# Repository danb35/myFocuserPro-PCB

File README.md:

# myFocuserPro-PCB
 KiCad schematic and board for myFocuserPro2: https://sourceforge.net/projects/arduinofocuscontrollerpro/

# Introduction
myFocuserPro is a DIY, Arduino-based focuser designed for use with telescopes.  The design, source code, schematics, PCB files (Gerbers), and extensive documentation are available at the link above.  So what am I doing in this repo?

Unfortunately, the Gerbers there have a few issues, most notably that the footprint for the reverse-polarity protection diode (D1 on the schematic) just doesn't fit the specified diode.  The specified "fix" for the problem is to file down the leads of the diode until they fit through the holes.  And while this should be a trivial thing to fix, editable source files for the schematic and board haven't been released.

To address this, I re-drew the schematic and PCB layout in KiCad 6.0.  [KiCad](https://www.kicad.org/) is free, open source electronics design software, so you can download it to edit these files as desired.

# Design changes
This schematic is identical to the M-MT-F-BT DRV8825-HW203 variation at SourceForge, as that's the recommended version for new builds.  I intend (and hope) that the schematic will be easier to read and follow, but there should not be any changes in the components or how they're connected.  I don't intend to do this for any other variations of the schematic.  Most of the reference designators (i.e., R3, C2, etc.) are identical, but KiCad has changed some of the semiconductors.  But I've made a few changes to the board layout.

First, of course, there's the change that drove the whole redesign--the footprint for D1 now actually fits the specified diode.  I've also replaced most of the places where pin headers had been used for off-board connections (e.g., for the stepper, the pushbuttons, the display, etc.) and replaced them with JST-XH connectors.  These provide some friction to prevent connections from coming loose inadvertently, and also polarize the connections (so, e.g., you can't plug in a LED backward).  The only exception to this is J3, the programming "switch."  I intend that this will be a jumper, not an externally accessible switch.

While the board size is similar to the original, it is not identical, and it will not fit in the 3D-printed case design that's posted on SourceForge.  As time permits, I'll try to prepare a case design that will work with this.

# Board Images
Here are images of the front and back of the board:

And here are 3D renders of (mostly) populated boards:

# Ordering
I don't sell these boards; you can have them made by any PCB fab you choose.  To do so, simply download Gerber/myFocuserPro.zip from this repo, upload it to your fab of choice, and have at it.  If you don't have a fab of choice, consider the two linked below, in which I have no financial interest (i.e., I'm not an affiliate, partner, or anything else; I don't make anything from your purchase of these boards--I'm just a customer of both services).

## OSHPark
OSHPark are an American company known for high-quality boards.  They'll produce three copies of your design for $5 per square inch, in purple, with gold plating.  This cost is often higher than the Chinese fabs, but they don't charge shipping, and you don't have to wait for shipping for China.  This board costs about $27 shipped for three copies as of this writing.  You can order boards using this link:
https://oshpark.com/profiles/danb35

## JLCPCB
[JLCPCB](https://jlcpcb.com/) are a Chinese PCB fab that I've been pretty happy with.  Their prices are low (starting at $2/5 boards), they produce the boards quickly, and they ship quickly via DHL.  The biggest drawback is the cost of shipping--at this writing, five boards will cost you $2, but the shipping is another $20 or more.

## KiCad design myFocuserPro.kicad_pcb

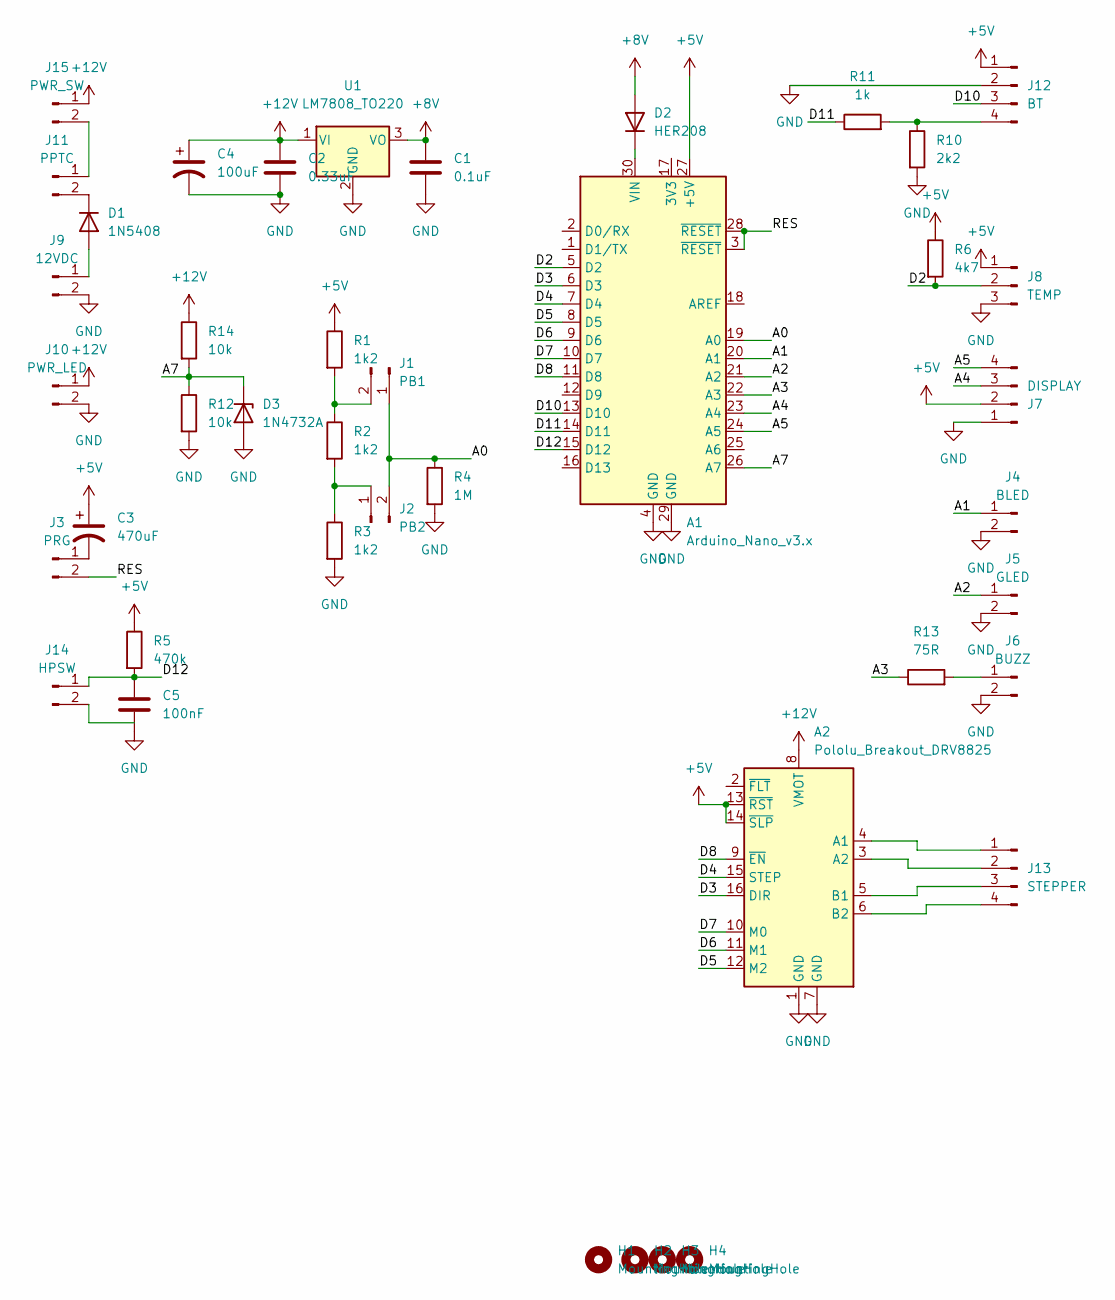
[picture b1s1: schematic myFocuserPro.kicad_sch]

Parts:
A1: Arduino_Nano_v3.x; Arduino_Nano
A2: Pololu_Breakout_DRV8825; Pololu_Breakout-16_15.2x20.3mm
C1: 0.1uF; C_Disc_D6.0mm_W2.5mm_P5.00mm
C2: 0.33uF; C_Disc_D6.0mm_W2.5mm_P5.00mm
C3: 470uF; CP_Radial_D8.0mm_P3.50mm
C4: 100uF; CP_Radial_D8.0mm_P3.50mm
C5: 100nF; C_Disc_D6.0mm_W2.5mm_P5.00mm
D1: 1N5408; D_DO-201AD_P15.24mm_Horizontal
D2: HER208; D_DO-15_P12.70mm_Horizontal
D3: 1N4732A; D_DO-15_P12.70mm_Horizontal
H1, H2, H3, H4: MountingHole; MountingHole_3.2mm_M3
J1: PB1; JST_XH_B2B-XH-AM_1x02_P2.50mm_Vertical
J2: PB2; JST_XH_B2B-XH-AM_1x02_P2.50mm_Vertical
J3: PRG; PinHeader_1x02_P2.54mm_Vertical
J4: BLED; JST_XH_B2B-XH-AM_1x02_P2.50mm_Vertical
J5: GLED; JST_XH_B2B-XH-AM_1x02_P2.50mm_Vertical
J6: BUZZ; JST_XH_B2B-XH-AM_1x02_P2.50mm_Vertical
J7: DISPLAY; JST_XH_B4B-XH-AM_1x04_P2.50mm_Vertical
J8: TEMP; JST_XH_B3B-XH-AM_1x03_P2.50mm_Vertical
J9: 12VDC; JST_XH_B2B-XH-AM_1x02_P2.50mm_Vertical
J10: PWR_LED; JST_XH_B2B-XH-AM_1x02_P2.50mm_Vertical
J11: PPTC; JST_XH_B2B-XH-AM_1x02_P2.50mm_Vertical
J12: BT; JST_XH_B4B-XH-AM_1x04_P2.50mm_Vertical
J13: STEPPER; JST_XH_B4B-XH-AM_1x04_P2.50mm_Vertical
J14: HPSW; JST_XH_B2B-XH-AM_1x02_P2.50mm_Vertical
J15: PWR_SW; JST_XH_B2B-XH-AM_1x02_P2.50mm_Vertical
R1, R2, R3: 1k2; R_Axial_DIN0309_L9.0mm_D3.2mm_P2.54mm_Vertical
R4: 1M; R_Axial_DIN0309_L9.0mm_D3.2mm_P12.70mm_Horizontal
R5: 470k; R_Axial_DIN0309_L9.0mm_D3.2mm_P2.54mm_Vertical
R6: 4k7; R_Axial_DIN0309_L9.0mm_D3.2mm_P12.70mm_Horizontal
R10: 2k2; R_Axial_DIN0309_L9.0mm_D3.2mm_P2.54mm_Vertical
R11: 1k; R_Axial_DIN0309_L9.0mm_D3.2mm_P2.54mm_Vertical
R12, R14: 10k; R_Axial_DIN0309_L9.0mm_D3.2mm_P12.70mm_Horizontal
R13: 75R; R_Axial_DIN0309_L9.0mm_D3.2mm_P12.70mm_Horizontal
U1: LM7808_TO220; TO-220-3_Vertical

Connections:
+5V: A1.27 (+5V), A2.13 (~RST), A2.14 (~SLP), C3.1, J7.2, J8.1, J12.1, R1.1, R5.1, R6.1
+8V: C1.1, D2.2 (A), U1.3 (VO)
+12V: A2.8 (VMOT), C2.1, C4.1, J10.1, J15.1, R14.1, U1.1 (VI)
/A0: A1.19 (A0), J1.1, J2.2, R4.1
/A1: A1.20 (A1), J4.1
/A2: A1.21 (A2), J5.1
/A3: A1.22 (A3), R13.1
/A4: A1.23 (A4), J7.3
/A5: A1.24 (A5), J7.4
/A7: A1.26 (A7), D3.1 (K), R12.1, R14.2
/D2: A1.5 (D2), J8.2, R6.2
/D3: A1.6 (D3), A2.16 (DIR)
/D4: A1.7 (D4), A2.15 (STEP)
/D5: A1.8 (D5), A2.12 (M2)
/D6: A1.9 (D6), A2.11 (M1)
/D7: A1.10 (D7), A2.10 (M0)
/D8: A1.11 (D8), A2.9 (~EN)
/D10: A1.13 (D10), J12.3
/D11: A1.14 (D11), R11.1
/D12: A1.15 (D12), C5.1, J14.1, R5.2
/RES: A1.3 (~RESET), A1.28 (~RESET), J3.2
GND: A1.4 (GND), A1.29 (GND), A2.1 (GND), A2.7 (GND), C1.2, C2.2, C4.2, C5.2, D3.2 (A), J4.2, J5.2, J6.2, J7.1, J8.3, J9.2, J10.2, J12.2, R3.2, R4.2, R10.2, R12.2, U1.2 (GND)
unnamed: A1.30 (VIN), D2.1 (K)
unnamed: A2.3 (A2), J13.2
unnamed: A2.4 (A1), J13.1
unnamed: A2.5 (B1), J13.3
unnamed: A2.6 (B2), J13.4
unnamed: C3.2, J3.1
unnamed: D1.1 (K), J11.2
unnamed: D1.2 (A), J9.1
unnamed: J1.2, R1.2, R2.1
unnamed: J2.1, R2.2, R3.1
unnamed: J6.1, R13.2
unnamed: J11.1, J15.2
unnamed: J12.4, R10.1, R11.2

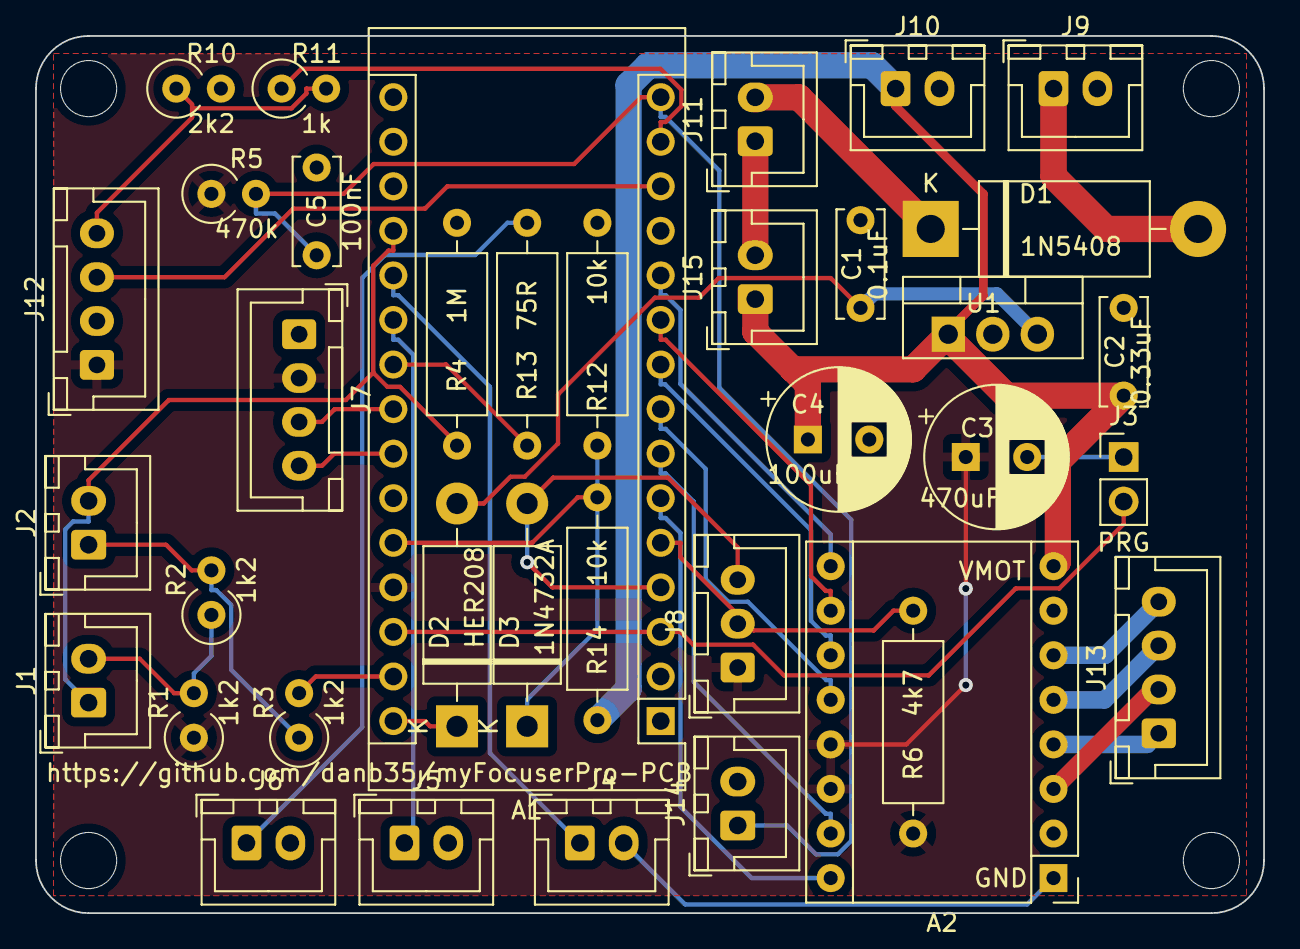
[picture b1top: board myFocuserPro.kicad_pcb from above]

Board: 2 copper layers, 70.0 x 50.0 mm, 41 parts (0 on the bottom side), 35 nets.

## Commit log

2022-03-02 Update JST footprints
2022-03-02 Update README and images
2022-03-20 Connect isolated grounds
2022-03-27 Update PCB layout
